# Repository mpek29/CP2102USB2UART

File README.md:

# CP2102USB2UART

## 🚀 Overview

An open-source reverse-engineered version of the CJMCU CP2102 USB to UART TTL adapter, based on the original component available [here](https://fr.aliexpress.com/item/1005006975725106.html). This project aims to provide insights into USB-to-serial communication and offer a customizable alternative for embedded system developers.

## 🎯 Purpose
- 🔍 **Reverse engineering**: Understanding the design and functionality of the CP2102USB2UART.
- 🛠️ **Skill development**: Enhancing expertise in PCB design and USB-to-serial communication.
- 🔄 **Future adaptation**: Leveraging this knowledge to develop custom USB-to-UART solutions for embedded systems.

## 📝 Features Comparison: Original vs. Reverse-Engineered

| Feature            | Original Module | Reverse-Engineered Version |
|--------------------|----------------|---------------------------|
| 🖥️ PCB Design        | Proprietary     | Open-source & customizable |
| 🔌 USB Connector     | Micro USB | Micro USB |
| 🏷️ Chipset           | CP2102          | CP2102 |
| 📌 Pin Mapping       | 6-Pin UART TTL  | 6-Pin UART TTL |
| ⚡ Supported Voltage | 3.3V / 5V       | 3.3V / 5V |
| 👐 Mechanical Drawing  |  |  |
| 📝 Reverse-Engineered Schematic | N/A |  |
| 📷 Photo             |  |  |

## 🛠️ How to Use
### 📌 Wiring Guide
| CP2102 Pin | Description |
|------------|-------------|
| TXD        | Transmit Data |
| RXD        | Receive Data |
| GND        | Ground |
| 3V3        | 3.3V Power Output |
| 5V         | 5V Power Output |
| DTR        | Data Terminal Ready |

## 🌟 License
This project is open-source. Feel free to use, modify, and contribute! 🚀

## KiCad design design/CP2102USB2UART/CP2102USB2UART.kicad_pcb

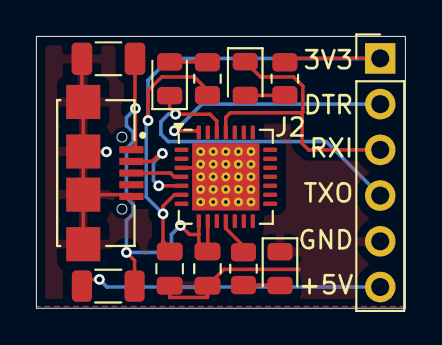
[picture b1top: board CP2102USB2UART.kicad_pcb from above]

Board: 2 copper layers, 20.5 x 15.1 mm, 13 parts (0 on the bottom side), 13 nets.

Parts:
C1: C; C_1206_3216Metric
C2, C3: C; C_0805_2012Metric
D1, D2, D3: LED; LED_0805_2012Metric
J1: Conn_01x06; PinHeader_1x06_P2.54mm_Vertical
J2: UJ2-MIBH-G-SMT-TR; CUI_UJ2-MIBH-G-SMT-TR
R1, R2, R3: R; R_0805_2012Metric
R4: R; R_1206_3216Metric
U1: CP2102; QFN-28-1EP_5x5mm_P0.5mm_EP3.75x3.75mm_ThermalVias

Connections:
+5V: J1.6, R4.1
D+: J2.3 (D+), U1.4 (D+)
D-: J2.2 (D-), U1.5 (D-)
DTR: J1.2, U1.28 (DTR)
GND: C1.1, C2.2, C3.2, D3.1 (K), J1.5, J2.5 (GND), U1.3 (GND), U1.29 (GND)
unnamed: D1.2 (A), R1.2
unnamed: D2.2 (A), R2.1
unnamed: D3.2 (A), R3.2
RXI: D2.1 (K), J1.3, U1.25 (RXD)
TXO: D1.1 (K), J1.4, U1.26 (TXD)
VCC: C1.2, C3.1, J2.1 (VCC), R4.2, U1.8 (VBUS), U1.9 (~RST)
VDD: C2.1, J1.1, R1.1, R2.2, U1.6 (VDD)
~SUSPEND: R3.1, U1.11 (~SUSPEND)

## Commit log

2025-02-19 Addition of some images to better describe the project
2025-03-01 bg top and bottom ready
2025-03-01 end of retroengineering
